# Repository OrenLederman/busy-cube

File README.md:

# busy-cube
Firmware and circuit design for a toy for toddlers - a simple box with 3 buttons that change colors when pressed.

Instructable link - not available yet

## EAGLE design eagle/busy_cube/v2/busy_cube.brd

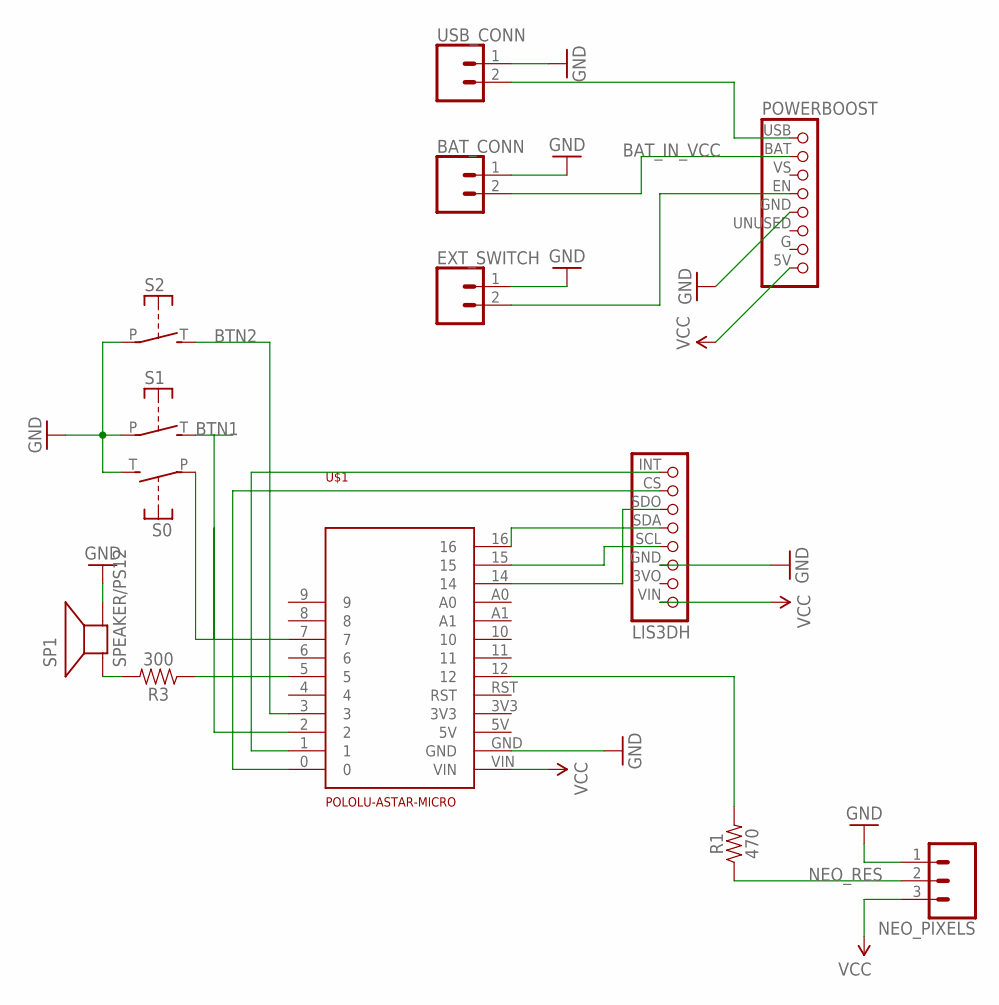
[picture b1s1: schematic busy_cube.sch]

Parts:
BAT_CONN: CONN_02-JST-2MM-SMT; JST-2-SMD
EXT_SWITCH: CONN_02-JST-2MM-SMT; JST-2-SMD
LIS3DH: ADA-LIS3DHPADS_ONLY; LIS3DH-1X08
NEO_PIXELS: CONN_03LONGPADS; 1X03_LONGPADS
POWERBOOST: ADA-POWERBOOST-1000CPADS-ONLY; POWERBOOST-1X08
R1: 470; AXIAL-0.3
R3: 300; AXIAL-0.3
S0, S1, S2: ADA-ARCADE-BTN30MM; ARCADE-BTN-30MM
SP1: SPEAKER/PS12; PS12
U$1: POLOLU-ASTAR-MICRO
USB_CONN: CONN_02-JST-2MM-SMT; JST-2-SMD

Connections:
3V3: U$1.3V3
5V: U$1.5V
BAT_IN_VCC: BAT_CONN.2 (1), POWERBOOST.BAT (3VO)
BTN1: S1.T (S), U$1.2
BTN2: S2.T (S), U$1.3
GND: BAT_CONN.1 (2), EXT_SWITCH.1 (2), LIS3DH.GND, NEO_PIXELS.1, POWERBOOST.GND (SDA), S0.T (S), S1.P, S2.P, SP1.P$2 (-), U$1.GND, USB_CONN.1 (2)
unnamed: LIS3DH.INT, U$1.1
unnamed: R1.P$2 (2), U$1.12
unnamed: LIS3DH.CS, U$1.0
unnamed: LIS3DH.SDO, U$1.14
unnamed: LIS3DH.SDA, U$1.16
unnamed: LIS3DH.SCL, U$1.15
unnamed: R3.P$2 (2), SP1.P$1 (+)
unnamed: EXT_SWITCH.2 (1), POWERBOOST.EN (SCL)
unnamed: S0.P, U$1.7
NEO_RES: NEO_PIXELS.2, R1.P$1 (1)
SPKR: R3.P$1 (1), U$1.5
USB_IN_VCC: POWERBOOST.USB (VIN), USB_CONN.2 (1)
VCC: LIS3DH.VIN, NEO_PIXELS.3, POWERBOOST.5V (INT), U$1.VIN

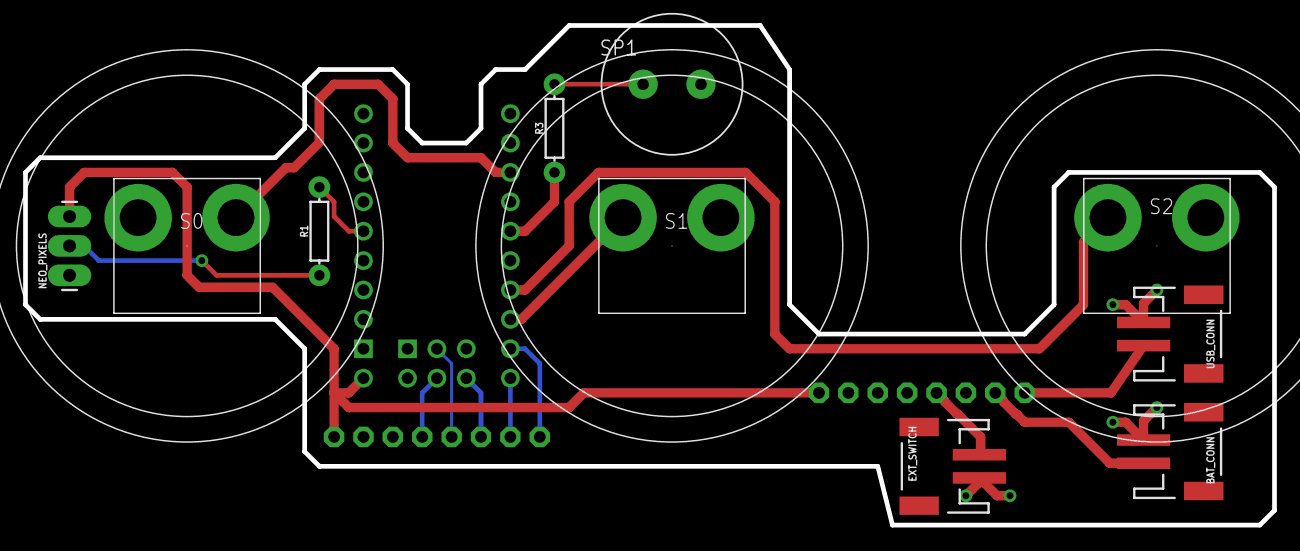
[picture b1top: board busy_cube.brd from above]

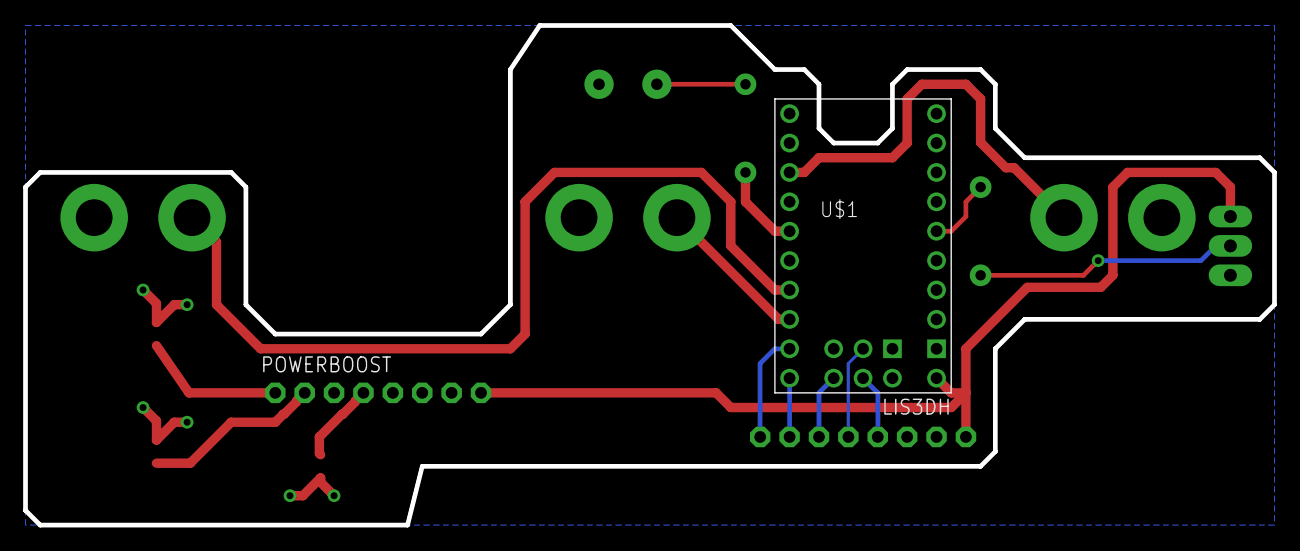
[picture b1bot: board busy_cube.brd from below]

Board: 2 copper layers, 108.0 x 43.2 mm, 13 parts (3 on the bottom side), 17 nets.

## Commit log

2017-12-25 Initial simple code
2017-12-25 Simple debounce
2017-12-27 Generalizing debouncing code. Adding more buttons
2017-12-27 Changing button colors
2017-12-27 Changing button colors, using wheel
2017-12-27 Fixed colors
2017-12-27 Generalized for X buttons
2017-12-27 Changed button pins
2017-12-27 Added delay to prevent neopixel from turning on
2017-12-31 Adding devices and basic board
2018-01-05 First attempt for wiring
2018-01-05 some more changes
2018-01-05 small changes
2018-01-05 Major changes since I need to switch to SPI with the accelerometer
2018-01-08 PCB changes
2018-01-10 PCB version for milling
2018-01-14 Code used in first version of the box
2018-01-15 Pressing the middle button wil now trigger low brightness mode
2018-01-17 simple sleep mode
2018-02-02 Switch is now connected to the EN pin
2018-02-03 Wider tracer for the button
2018-02-14 small changes, adding (unfinished) v2 of the board design
2018-03-19 Cleaner version of v2
2018-03-19 Large pads and holes for the buttons
2018-03-19 Some updates based on Sparkfun's DRU rules
2019-11-24 Not sure what's in this commit
